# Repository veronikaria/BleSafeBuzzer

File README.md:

# SafeGuard Buzzer v1 — CR2450 One-Side Assembly

SafeGuard Buzzer is a BLE-controlled backpack or laptop-case alarm module paired with SafeGuard Ping. It uses a passive magnetic sounder so firmware can generate alarm patterns and escalation. KiCad is the source of truth for the electrical and PCB design.

## Current hardware

- BLE module: Renesas/Dialog DA14531MOD-00F01002, LCSC C5360767
- Battery: replaceable CR2450 primary coin cell
- Battery holder: MYOUNG MY-2450-03, LCSC C2988622
- Buzzer: FUET FUET-1365-3V passive magnetic SMD sounder, LCSC C417422
- Power switch: PCM12SMTR, LCSC C221841
- Buzzer driver: AO3400A N-channel MOSFET, LCSC C20917
- Clamp diode: BAT54WS, LCSC C22629
- Status indicator: red 0603 LED with 2.2 kΩ resistor
- Debug: compact VCC, GND, SWDIO, and SWCLK pads
- Current measurement: bridgeable JP1 link
- No charger, USB, user silence/test button, or external reset supervisor

Power path:

```text
CR2450 -> S1 ON/OFF switch -> JP1 current-measurement bridge -> VCC
```

Buzzer drive path:

```text
DA14531MOD PWM/GPIO -> 100 ohm gate resistor -> AO3400A -> passive buzzer
                                      |
                                  100 kohm pulldown
```

## Mechanical configuration

- Board size: 65.0 × 40.0 mm
- BT1: Top at `(24.0, 24.0)`
- BZ1: Top at `(48.0, 31.0)`, near the edge for a future hidden acoustic opening
- S1: Top at `(6.0, 7.0)`, left-edge accessible
- U1: Top at `(54.5, 10.5)`, with the antenna at the board edge
- All 13 assembled BOM/CPL components are on Top
- Bottom contains copper and traces only; it has no assembled components or footprints
- Battery metal does not overlap the DA14531MOD antenna keepout

The PCB remains a two-copper-layer design, but JLC assembly is **Top Side only**.

## Active KiCad files

- Schematic: `SafeGuardBuzzer_v1.kicad_sch`
- PCB: `SafeGuardBuzzer_v1.kicad_pcb`
- Project-local footprints: `SafeGuardBuzzer_Local.pretty/`
- Project-local symbols: `SafeGuardBuzzer_Local.kicad_sym`

## Validation status

- ERC: 0 errors and 10 footprint-library configuration warnings
- DRC: 0 real electrical or fabrication errors
- Unconnected items: 0
- Shorts: 0
- Clearance errors: 0
- Antenna-keepout violations: 0
- Remaining DRC warnings: missing configured stock footprint libraries, one U1 library-copy mismatch, and two clipped-silkscreen warnings
- Schematic parity warnings are metadata/value differences and do not change connectivity or the verified manufacturing BOM/CPL

## JLC manufacturing outputs

Output folder:

```text
Manufacturing_Final_Buzzer_v1_CR2450_OneSide_JLC/
```

Upload these files:

- Gerber/drill ZIP: `SafeGuardBuzzer_v1_CR2450_OneSide_JLC_Gerber_Drill_Upload_CORRECTED.zip`
- BOM: `SafeGuardBuzzer_v1_CR2450_OneSide_JLC_BOM.csv`
- CPL: `SafeGuardBuzzer_v1_CR2450_OneSide_JLC_CPL.csv`

Do not upload `SafeGuardBuzzer_v1_CR2450_OneSide_JLC_Gerber_Drill_Upload.zip`. That older archive contains `SafeGuardBuzzer_v1-drl_map.gbr`, whose legend extends outside the PCB and can cause JLCPCB to report an incorrect 75 × 70 mm size.

The corrected ZIP contains only the fabrication Gerbers, the actual Excellon drill file, and the Gerber job file. Its Edge.Cuts profile is exactly 65 × 40 mm.

J1, J2, and JP1 are copper-only debug/test/current-measurement pads and are intentionally excluded from both BOM and CPL.

## JLC order settings and preview checklist

1. Select a two-layer PCB.
2. Select **Top Side only** assembly.
3. Confirm detected board size is 65 × 40 mm.
4. Confirm all 13 CPL placements are Top; Bottom should contain no placements.
5. Do not accept automatic component alignment if the uploaded CPL already overlays the Gerbers correctly.
6. Confirm BT1 is MY-2450-03 / C2988622, BZ1 is FUET-1365-3V / C417422, S1 is PCM12SMTR / C221841, and U1 is DA14531MOD / C5360767.
7. Confirm buzzer, diode, LED, MOSFET, switch, and module orientation in the placement preview.
8. Confirm the DA14531MOD antenna keepout remains free of copper and battery metal.

## Prototype note

CR2450 cells have less pulse-current capability than CR123A cells. The selected buzzer and bulk capacitance are intended for a moderate alarm, but sound pressure and battery droop should be measured on assembled prototypes during a full one-to-two-minute alarm cycle.

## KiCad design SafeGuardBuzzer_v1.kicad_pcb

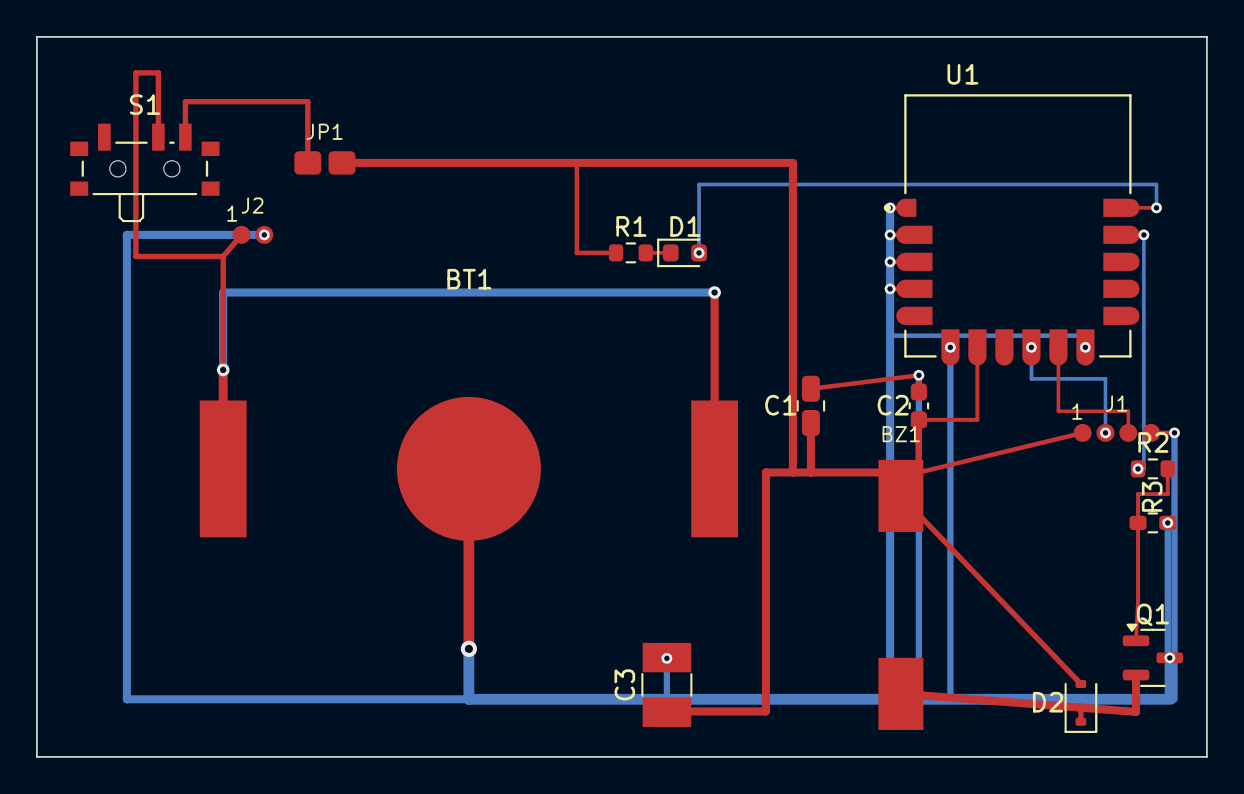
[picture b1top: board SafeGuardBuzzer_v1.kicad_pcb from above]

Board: 2 copper layers, 65.0 x 40.0 mm, 16 parts (0 on the bottom side), 11 nets.

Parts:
BT1: MYOUNG MY-2450-03 CR2450 holder; BatteryHolder_MYOUNG_MY-2450-03_C2988622_CR2450
BZ1: FUET-1365-3V; Buzzer_FUET_FUET-1365-3V_C417422
C1: 10uF; C_0805_2012Metric
C2: 100nF; C_0603_1608Metric
C3: 100uF; C_1210_3225_Samsung_CL32A107MQVNNNE_C49066
D1: Red LED; LED_0603_1608Metric
D2: BAT54WS; D_SOD-323
J1: SWD_DEBUG; TP_SWD_1x04_1.27mm_Compact
J2: VBAT_GND_TEST; TP_1x02_1.27mm_Compact
JP1: CURRENT_MEAS; TP_Current_Jumper_2Pad_Compact
Q1: AO3400A; SOT-23
R1: 2.2k; R_0603_1608Metric
R2: 100; R_0603_1608Metric
R3: 100k; R_0603_1608Metric
S1: PCM12 ON/OFF; SW_SPDT_PCM12
U1: DA14531MOD-00F01002; XCVR_DA14531MOD-00F01002

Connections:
BUZZER_NEG: BZ1.2, D2.1, Q1.2
BUZZER_PWM: R2.1, U1.J15
BUZZER_PWM_GATE: Q1.1, R2.2, R3.1
GND: BT1.2, C1.2, C2.2, C3.2, J1.4, J2.2, Q1.3, R3.2, U1.J1, U1.J2, U1.J3, U1.J4, U1.J6, U1.J11
LED_A: D1.1, R1.2
LED_STATUS: D1.2, U1.J16
SWCLK: J1.3, U1.J10
SWDIO: J1.2, U1.J9
VBAT_RAW: BT1.1, J2.1, S1.2
VBAT_SW: JP1.1, S1.3
VCC: BZ1.1, C1.1, C2.1, C3.1, D2.2, J1.1, JP1.2, R1.1, U1.J7

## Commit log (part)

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2026-06-28 Create SafeGuard Buzzer v1 schematic candidate
2026-06-29 Resolve Buzzer CR123A holder footprint
2026-06-29 Create initial Buzzer PCB rough layout candidate
2026-06-29 Clean Buzzer RF keepout and DRC before routing
2026-06-29 Route initial Buzzer power path
2026-06-29 Add Buzzer project footprints and project settings
2026-06-29 Complete Buzzer v1 routing
2026-06-29 Generate final Buzzer v1 JLC manufacturing package
